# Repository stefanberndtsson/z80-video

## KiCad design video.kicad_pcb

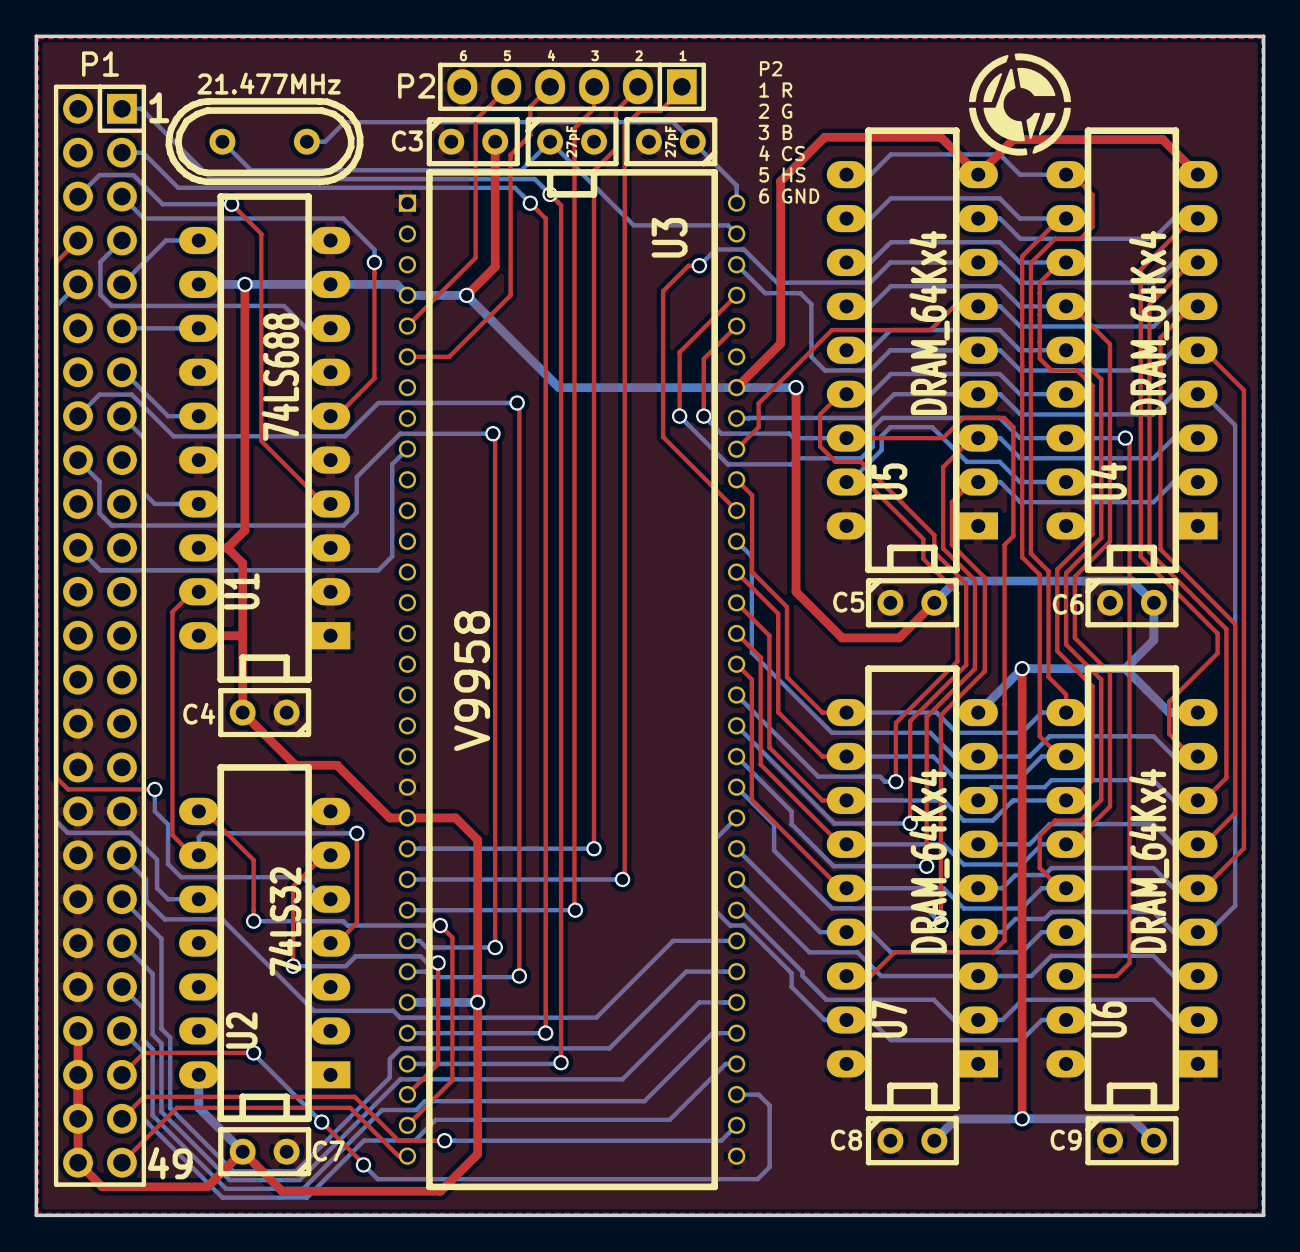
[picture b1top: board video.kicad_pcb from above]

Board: 2 copper layers, 71.0 x 68.2 mm, 19 parts (0 on the bottom side), 54 nets.

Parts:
21.477MHz: 21.477MHz; Crystal_HC49-U_Vertical
27pF, 27pF#2: 27pf; Capacitor3MMDiscRM2.5
C3, C4, C5, C6, C7, C8, C9: C; Capacitor3MMDiscRM2.5
P1: CONN_25X2; Socket_Strip_Straight_2x25
P2: CONN_6; Socket_Strip_Straight_1x06
U1: 74LS688; DIP-20__300_ELL
U2: 74LS32; DIP-14__300_ELL
U3: V9958; DIP64-70mil-900_ELL
U4, U5, U6, U7: DRAM_64Kx4; DIP-18__300_ELL

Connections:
/A0: P1.1, U3.29
/A1: P1.3, U3.28
/A2: P1.5, U1.6
/A3: P1.7, U1.8
/A4: P1.9, U1.11
/A5: P1.11, U1.13
/A6: P1.13, U1.15
/A7: P1.15, U1.17
/AD0: U3.49, U4.14, U5.14, U6.14, U7.14
/AD1: U3.50, U4.13, U5.13, U6.13, U7.13
/AD2: U3.51, U4.12, U5.12, U6.12, U7.12
/AD3: U3.52, U4.11, U5.11, U6.11, U7.11
/AD4: U3.53, U4.8, U5.8, U6.8, U7.8
/AD5: U3.54, U4.7, U5.7, U6.7, U7.7
/AD6: U3.55, U4.10, U5.10, U6.10, U7.10
/AD7: U3.56, U4.6, U5.6, U6.6, U7.6
/BLUE: P2.3, U3.24
/CAS0: U3.61, U4.16, U6.16
/CAS1: U3.60, U5.16, U7.16
/CD0: P1.35, U3.40
/CD1: P1.37, U3.39
/CD2: P1.39, U3.38
/CD3: P1.41, U3.37
/CD4: P1.43, U3.36
/CD5: P1.45, U3.35
/CD6: P1.47, U3.34
/CD7: P1.49, U3.32
/CSR: U2.8, U3.31
/CSW: U2.6, U3.30
/CSYNC: P2.4, U3.6
/GREEN: P2.2, U3.22
/HSYNC: P2.5, U3.5
/INT: P1.18, U3.25
/IORQ: P1.6, U1.4
/RAS: U3.62, U4.5, U5.5, U6.5, U7.5
/RD: P1.10, U2.10
/RD0: U3.41, U6.2, U7.2
/RD1: U3.42, U6.3, U7.3
/RD2: U3.43, U6.15, U7.15
/RD3: U3.44, U6.17, U7.17
/RD4: U3.45, U4.2, U5.2
/RD5: U3.46, U4.3, U5.3
/RD6: U3.47, U4.15, U5.15
/RD7: U3.48, U4.17, U5.17
/RED: P2.1, U3.23
/RESET: P1.22, U3.9
/VDPCS: U1.19, U2.4, U2.9
/WAIT: P1.16, U3.26
/WE: U3.57, U4.4, U5.4, U6.4, U7.4
/WR: P1.8, U2.5
GND: 27pF.2, 27pF#2.2, C3.1, C4.1, C5.1, C6.1, C7.1, C8.1, C9.1, P1.30, P1.32, P1.33, P1.34, P1.36, P1.38, P1.40, P1.42, P2.6, U1.1, U1.2, U1.3, U1.5, U1.7, U1.10, U1.14, U1.16, U2.7, U3.1, U3.20, U3.33, U4.1, U4.18, U5.1, U5.18, U6.1, U6.18, U7.1, U7.18
unnamed: 21.477MHz.2, 27pF.1, U3.63
unnamed: 21.477MHz.1, 27pF#2.1, U3.64
VCC: C3.2, C4.2, C5.2, C6.2, C7.2, C8.2, C9.2, P1.44, P1.46, P1.48, P1.50, U1.9, U1.12, U1.18, U1.20, U2.14, U3.4, U3.21, U3.27, U3.58, U4.9, U5.9, U6.9, U7.9

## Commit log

2014-08-15 Initial
